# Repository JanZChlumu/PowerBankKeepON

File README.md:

# Keep powerbank on

>This project is based on ideas from [Andreas Spiess YouTube video ](https://www.youtube.com/watch?v=SgV6_Y_sg4k&t=782s&ab_channel=AndreasSpiess)

The main idea is to keep powerbank on if her load is less than powerbank on threshold.
Every powerbank detect drawn current if current is less than cca 5mA the powebank enable timeout for switch off.
The tool is trying to catch the maximum power off timeout and connect some load before timeout. It will postpone (reset) automatic power off.

Example with load connection:

## PCB
Was designed in KiCad... see folder [folder](PCB)

## How to use the tool
1. **Learning mode**
<br> press the button and connect powerbank. The GREEN led will blink 3times that means the powerbank is in learning mode. The tool is waiting until the powerbank will be automatically powered off. This time is stored in internal eeprom.
2. **Working mode**  
<br>switch on or Reconnect the powerbank. If tool correctly stored a power off time in step one and this time is bigger than 1 second, the GREEN led will be ON for 5 seconds.
<br> If learning process failed, the GREEN and RED leds blinks 3 times and tool is automatically switched to 1st point - learning mode.

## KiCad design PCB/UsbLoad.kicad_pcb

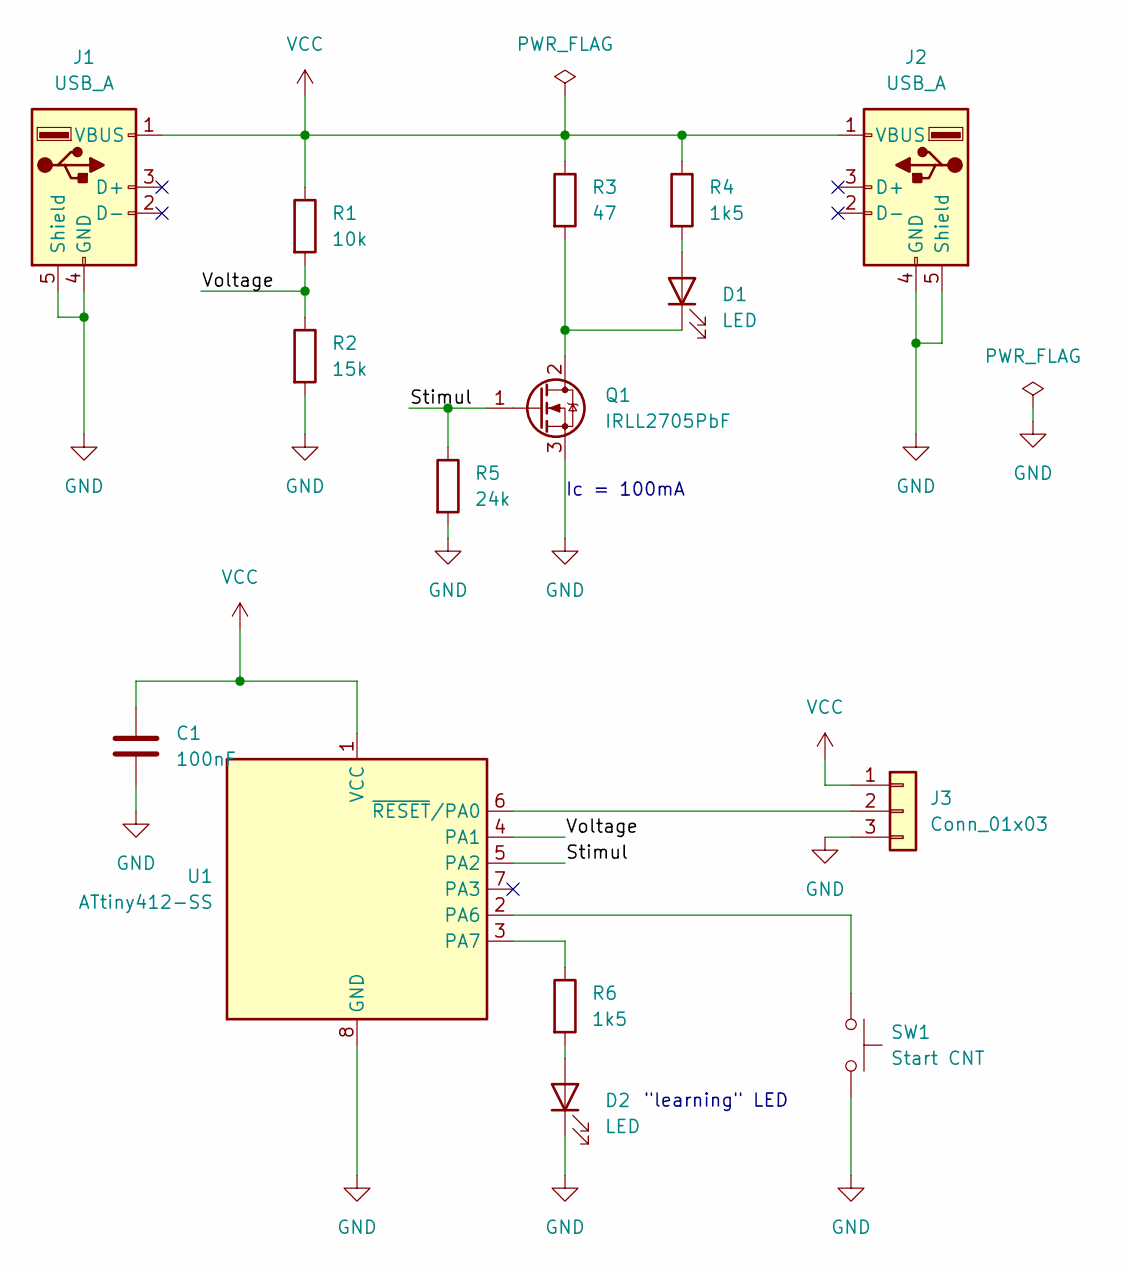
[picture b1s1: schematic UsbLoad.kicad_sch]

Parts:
C1: 100nF; R_0603_1608Metric
D1, D2: LED; LED_0603_1608Metric
J1: USB_A; USB_A_Molex_18161_Horizontal
J2: USB_A; USB_A_CONNFLY_DS1095-WNR0
J3: Conn_01x03; PinSocket_1x03_P2.54mm_Vertical
Q1: IRLL2705PbF; SOT-223-3_TabPin2
R1: 10k; R_0603_1608Metric
R2: 15k; R_0603_1608Metric
R3: 47; R_2010_5025Metric_Pad1.40x2.65mm_HandSolder
R4, R6: 1k5; R_0603_1608Metric
R5: 24k; R_0603_1608Metric
SW1: Start CNT; SW_Tactile_SPST_Angled_PTS645Vx58-2LFS
U1: ATtiny412-SS; SOIC-8_3.9x4.9mm_P1.27mm

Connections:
/Stimul: Q1.1 (G), R5.1, U1.5 (PA2)
/Voltage: R1.2, R2.1, U1.4 (PA1)
GND: C1.1, D2.1 (K), J1.4 (GND), J1.5 (Shield), J2.4 (GND), J2.5 (Shield), J3.3, Q1.3 (S), R2.2, R5.2, SW1.2, U1.8 (GND)
unnamed: D1.2 (A), R4.2
unnamed: D1.1 (K), Q1.2 (D), R3.2
unnamed: D2.2 (A), R6.2
unnamed: J3.2, U1.6 (~RESET/PA0)
unnamed: SW1.1, U1.2 (PA6)
unnamed: R6.1, U1.3 (PA7)
VCC: C1.2, J1.1 (VBUS), J2.1 (VBUS), J3.1, R1.1, R3.1, R4.1, U1.1 (VCC)

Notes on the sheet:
"learning" LED
Ic = 100mA

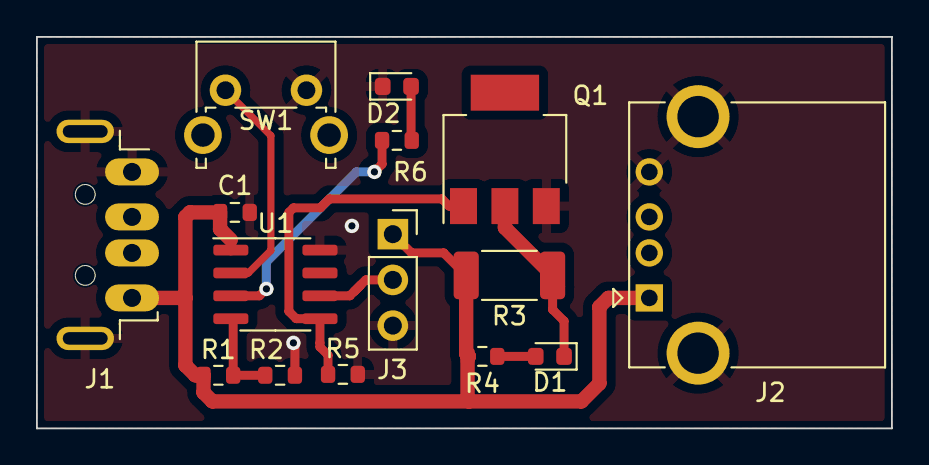
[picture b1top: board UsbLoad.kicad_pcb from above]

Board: 2 copper layers, 47.5 x 21.8 mm, 15 parts (0 on the bottom side), 10 nets.

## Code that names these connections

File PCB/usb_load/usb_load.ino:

#include <EEPROM.h>

#define PIN_BTN PIN_PA6
#define PIN_VOLTAGE PIN_PA1
#define PIN_STIMUL PA2

static unsigned int tick = 0;
static bool store;
unsigned int addr = 0;

void setup() {
  pinMode(PIN_BTN, INPUT_PULLUP);

  if(digitalRead(PIN_BTN) == LOW)
  {
    //button pressed start counting
    store = true;
    EEPROM.put(addr, tick);
  }
  else
  {
    store = false;
  }

}

void loop() {
  // put your main code here, to run repeatedly:
  EEPROM.write(addr, tick);
  delay(1000);
}

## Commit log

2024-04-26 PCB design
2024-05-09 first version of code... :)
2024-05-16 Rename PCB_3D Viewer.png to PCB_3D_Viewer.png
